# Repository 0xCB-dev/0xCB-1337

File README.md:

# 0xcb-1337
## Mechanical macropad with OLED running QMK

Licence | OSHWA
:-------------------------:|:-------------------------:
 | 

### Available here:

[KeebSupply](https://keeb.supply/products/0xcb-1337)

### QMK:

[keyboards/0xcb/1337/](https://github.com/qmk/qmk_firmware/tree/master/keyboards/0xcb/1337)

#### Flashing:

* `qmk clone`
* `cd qmk_firmware`
* `export LTO=Y`
* Press switch 1 while plugging in to go into dfu mode (or the reset button)
* `make 0xcb/1337:via:flash`

### Assembly:

You can use the [humanpnp](https://files.0xcb.dev/0xCB-1337/humanpnp.html) to easily place components.

### PCB:
KiCad 6 stable release - using these [libs](https://github.com/0xCB-dev/0xcb-libs)

[Schematic](https://github.com/0xCB-dev/0xcb-1337/blob/main/rev4.0/1337-v4.0.pdf)

Top | Bottom
:-------------------------:|:-------------------------:
  |  

### Case 3D files:

[STLs](https://github.com/0xCB-dev/0xcb-1337/tree/main/rev4.0/case/STL)

### PCB 3D files:

[FreeCAD](https://github.com/0xCB-dev/0xcb-1337/tree/main/rev4.0/1337-freecad.FCStd)

[STEP](https://github.com/0xCB-dev/0xcb-1337/tree/main/rev4.0/1337-v4.0.step)

[WRL](https://github.com/0xCB-dev/0xcb-1337/tree/main/rev4.0/1337-v4.0.wrl)

#### BOM:
 References                        | Value        | Quantity | Part Nb.            
-----------------------------------|--------------|----------|---------------------
 C2, C4, C6, C7, C8, C10, C12, C14 | 100n         | 8        | C478888             
 C3, C5, C9                        | 1u           | 3        | C29936              
 C11, C13                          | 22p          | 2        | C85969              
 C1                                | 10u          | 1        | C85713              
 R1, R2                            | 5.1k         | 2        | C23186              
 R3, R4                            | 22           | 2        | C174301             
 R5, R6                            | 10k          | 2        | C98220              
 D1, D2, D3, D4, D5, D6, D7, D8    | SK6812MINI-E | 8        | SK6812MINI-E        
 D10, D11, D12, D13                | WS2812B      | 4        | C114586             
 D9                                | SMF5.0CA     | 1        |  576-SMF5.0CA       
 U2                                | USBLC6-2SC6  | 1        | C7519               
 U3                                | ATMEGA32U4   | 1        | ATMEGA32U4RC-MU-ND  
 Y1                                | 16MHz        | 1        | C389842             
 F1                                | 1A           | 1        | C369150             
 SW1                               | SW_Push      | 1        | C318884             
 FB1, FB2                          | 600R         | 2        | C74330              
 RN1                               | 10k          | 1        | C109324             
 J1                                | USB_IN       | 1        | 900-2169900001CT-ND

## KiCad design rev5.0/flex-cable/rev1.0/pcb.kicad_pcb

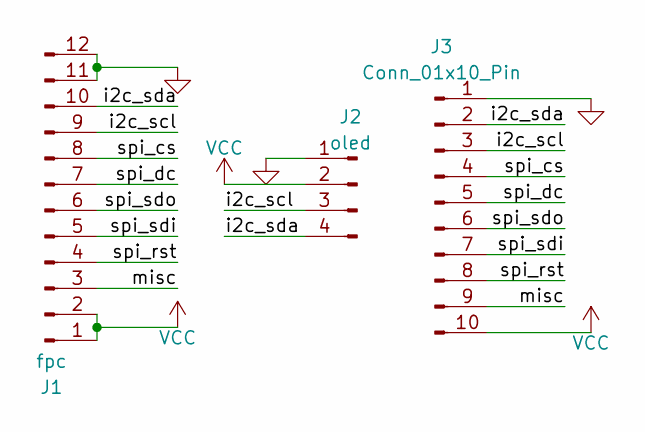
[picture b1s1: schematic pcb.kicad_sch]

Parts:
J1: fpc; FFC-SMD_12P-P0.50_X05B20U12T
J2: oled
J3: Conn_01x10_Pin; PinHeader_1x10_P2.54mm_Vertical

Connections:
/i2c_scl: J1.9, J2.3, J3.3
/i2c_sda: J1.10, J2.4, J3.2
/misc: J1.3, J3.9
/spi_cs: J1.8, J3.4
/spi_dc: J1.7, J3.5
/spi_rst: J1.4, J3.8
/spi_sdi: J1.5, J3.7
/spi_sdo: J1.6, J3.6
GND: J1.11, J1.12, J2.1, J3.1
VCC: J1.1, J1.2, J2.2, J3.10

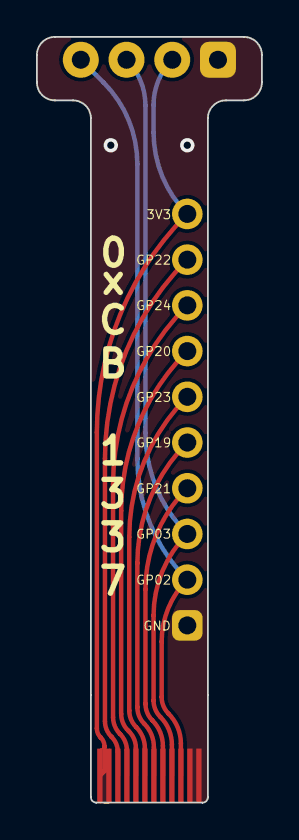
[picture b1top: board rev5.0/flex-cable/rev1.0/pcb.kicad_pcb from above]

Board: 2 copper layers, 12.5 x 42.5 mm, 3 parts (1 on the bottom side), 10 nets.

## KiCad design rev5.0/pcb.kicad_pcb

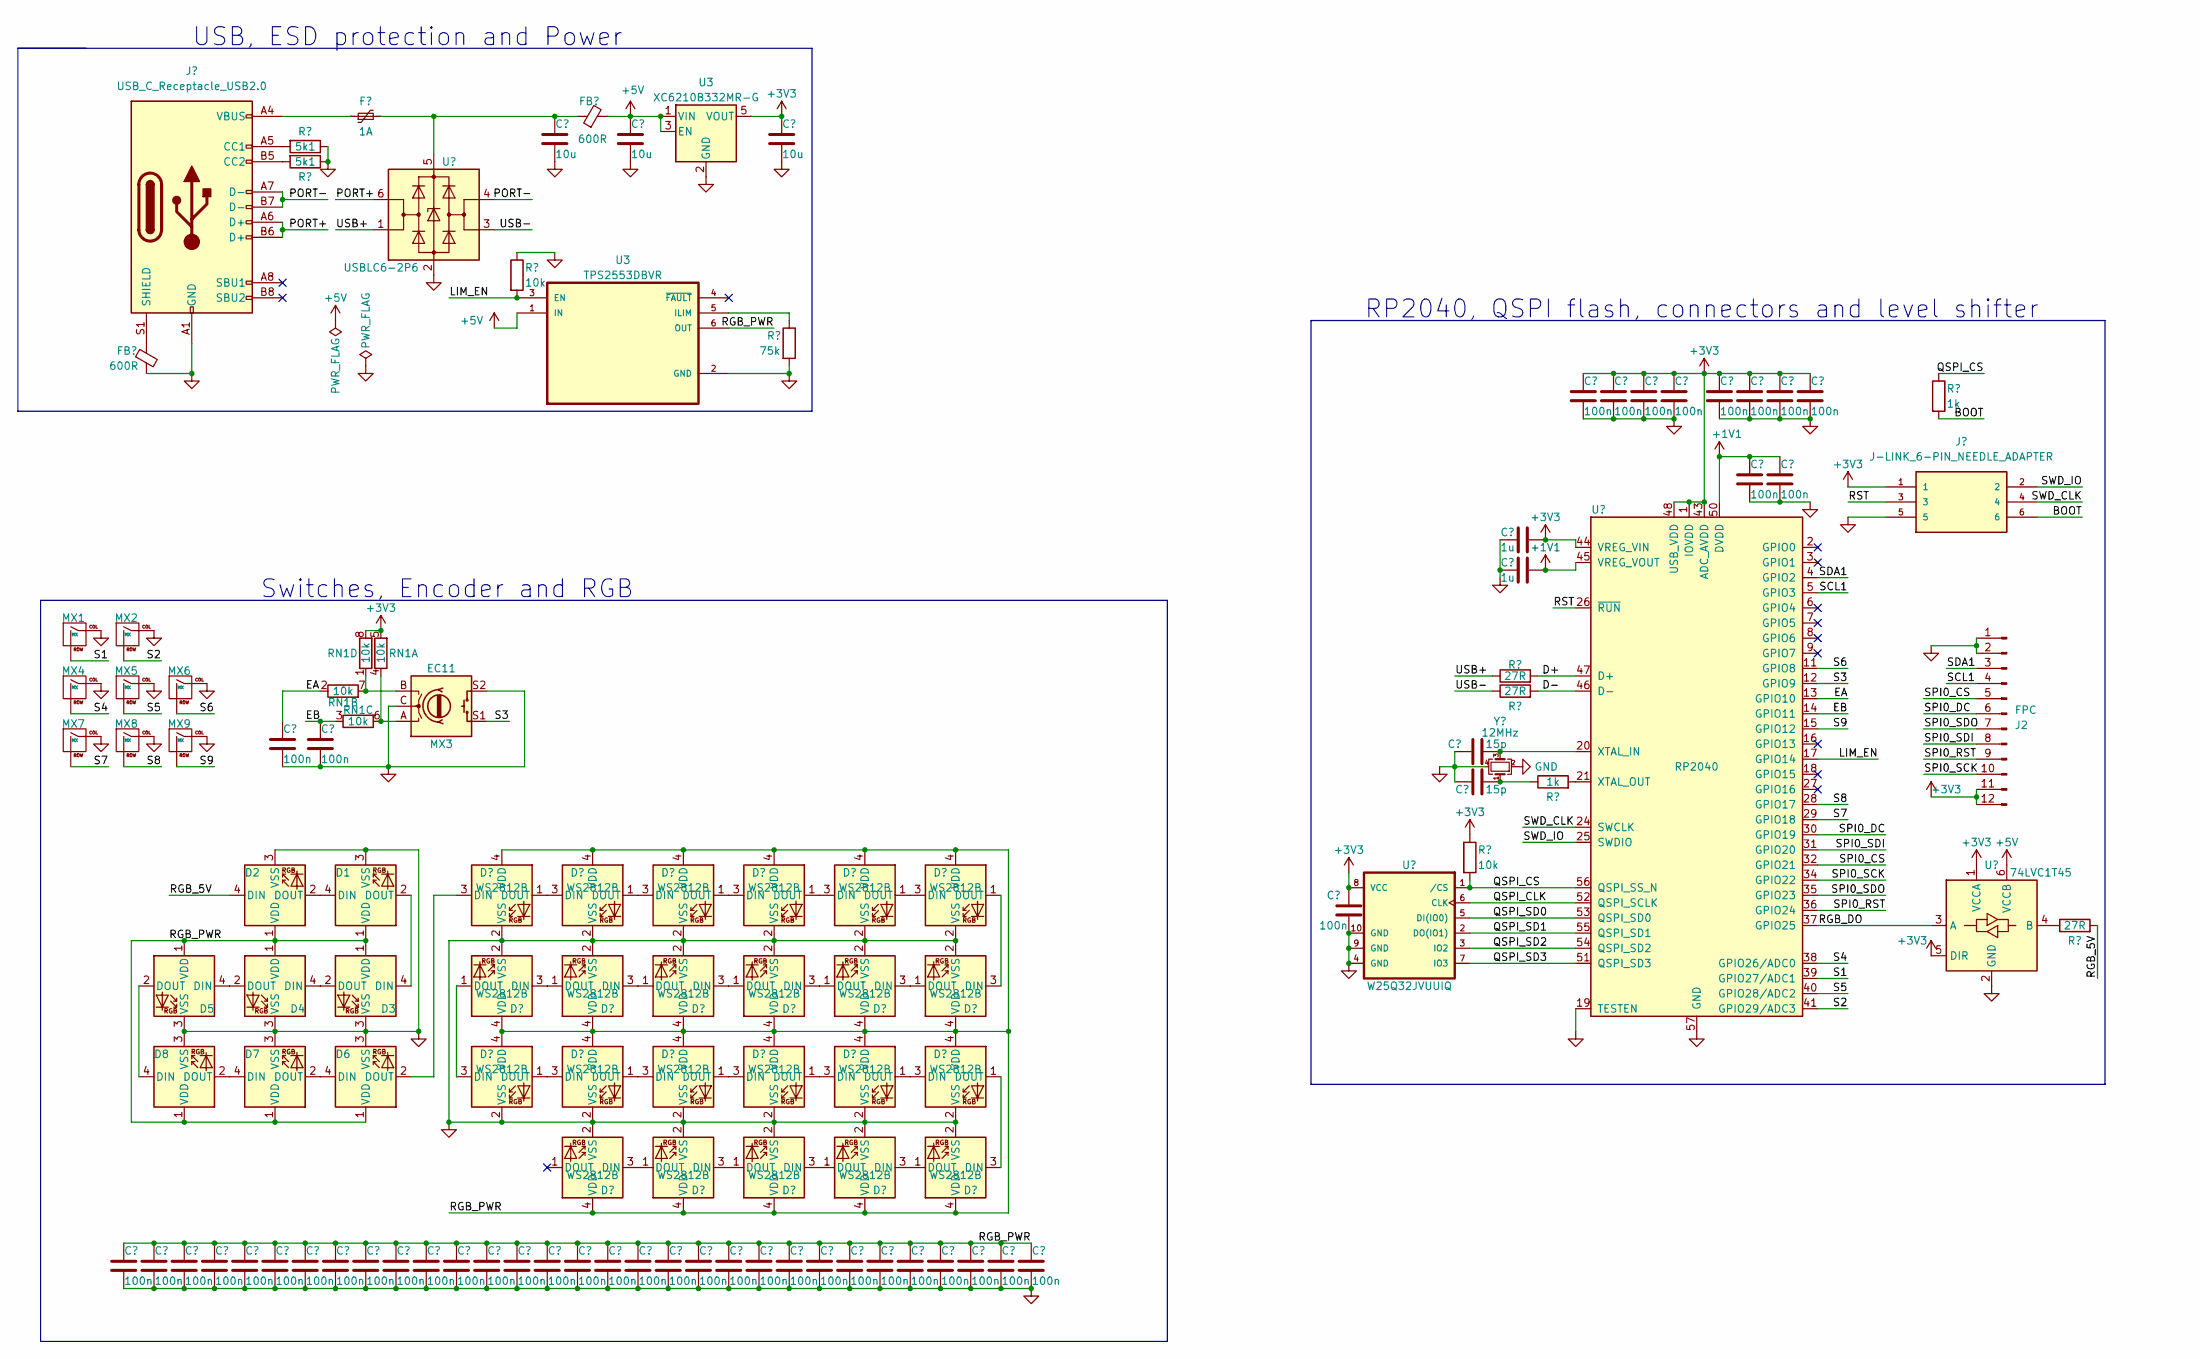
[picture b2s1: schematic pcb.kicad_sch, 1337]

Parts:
C1, C2, C3, C4, C5, C6, C7, C8, C9, C12, C13, C14, C15, C16, C18, C19, C20, C21, C23, C24, C25, C27, C28, C29, C30, C31, C32, C33, C34, C35, C36, C38, C39, C41, C42, C43, C44, C45, C46, C47, C48, C49, C50, C51: 100n; C_0201_0603Metric; MPN CL05B104KO5NNNC; LCSC C576431
C10, C11, C17: 10u; C_0402_1005Metric; MPN CL05A106MQ5NUNC; JLC Basic Y
C22, C26: 1u; C_0201_0603Metric; MPN CL05A105KA5NQNC; LCSC C237458
C37, C40: 15p; C_0201_0603Metric; MPN 0402CG150J500NT; LCSC C85891
D1, D2, D3, D4, D5, D6, D7, D8: SK6812MINI-E; MX_SK6812MINI-E; LCSC C5149201
D9, D10, D11, D12, D13, D14, D15, D16, D17, D18, D19, D20, D21, D22, D23, D24, D25, D26, D27, D28, D29, D30, D31: WS2812B; LED_WS2812B-2020_PLCC4_2.0x2.0mm; MPN WS2812B-2020; LCSC C2976072
F1: 1A; Fuse_0603_1608Metric; MPN MF-FSMF050X-2; LCSC C210357
FB1, FB2: 600R; R_0402_1005Metric; MPN BLM15PX601SN1D; JLC Basic N
J1: USB_C_Receptacle_USB2.0; GT-USB-7014C; MPN GT-USB-7014C; JLC Basic N
J2: FPC; FFC-SMD_12P-P0.50_X05B20U12T; LCSC C388698
J3: J-LINK_6-PIN_NEEDLE_ADAPTER; J-LINK_6-PIN_NEEDLE_ADAPTER_SMALL; MPN TC2030-ALT-NL
MX1, MX2, MX4, MX5, MX6, MX7, MX8, MX9: MX; SW_Hotswap_Kailh_1.00u; LCSC C5156480
MX3: EC11; Part Nb. PEC11L-4125F-S0020-ND; LCSC C143817
R1, R2: 5k1; R_0201_0603Metric; MPN 0402WGF5101TCE; LCSC C473460
R3, R8, R9: 27R; R_0201_0603Metric; MPN 0402WGF270JTCE; LCSC C273295
R4, R7: 10k; R_0201_0603Metric; MPN 0402WGF1002TCE; LCSC C138117
R5: 75k; R_0201_0603Metric; MPN 0402WGF1002TCE; LCSC C25744
R6, R10: 1k; R_0201_0603Metric; MPN 0402WGF1001TCE; LCSC C138165
RN1: 10k; R_Array_Convex_4x0603; Part Nb. MNR14103RTR-ND; LCSC C914793
U1: USBLC6-2P6; SOT-666; MPN USBLC6-2P6; JLC Basic N
U3: TPS2553DBVR; SOT95P280X145-6N; LCSC C55266
U4: 74LVC1T45; SOT-563; MPN SN74LVC1T45DRLR; JLC Basic N
U5: W25Q32JVUUIQ; MPN W25Q32JVUUIQ; LCSC C2999380
U6: RP2040; RP2040-QFN-56; MPN RP2040; LCSC C2040
Y1: 12MHz; Crystal_SMD_2520-4Pin_2.5x2.0mm; MPN 2TJ412000HYGBC; LCSC C2149204

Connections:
+1V1: C22.2, C25.1, C39.1, U6.23 (DVDD), U6.45 (VREG_VOUT), U6.50 (DVDD)
/BOOT: J3.6, R6.2
/D+: R8.2, U6.47 (D+)
/D-: R9.2, U6.46 (D-)
/EA: C7.1, RN1.2 (R2.1), U6.13 (GPIO10)
/EB: C8.1, RN1.3 (R3.1), U6.14 (GPIO11)
/PORT+: J1.A6 (D+), J1.B6 (D+), U1.6 (I/O1)
/PORT-: J1.A7 (D-), J1.B7 (D-), U1.4 (I/O2)
/QSPI_CLK: U5.6 (CLK), U6.52 (QSPI_SCLK)
/QSPI_CS: R6.1, R7.2, U5.1 (/CS), U6.56 (QSPI_SS_N)
/QSPI_SD0: U5.5 (DI(IO0)), U6.53 (QSPI_SD0)
/QSPI_SD1: U5.2 (DO(IO1)), U6.55 (QSPI_SD1)
/QSPI_SD2: U5.3 (IO2), U6.54 (QSPI_SD2)
/QSPI_SD3: U5.7 (IO3), U6.51 (QSPI_SD3)
/RGB_5V: D2.4 (DIN), R3.2
/RGB_DO: U4.3 (A), U6.37 (GPIO25)
/RGB_PWR: C1.1, C2.1, C3.1, C4.1, C5.1, C6.1, C9.1, C12.1, C13.1, C14.1, C15.1, C16.1, C18.1, C19.1, C20.1, C28.1, C29.1, C30.1, C31.1, C36.1, C41.1, C42.1, C43.1, C44.1, C45.1, C46.1, C47.1, C48.1, C49.1, C50.1, C51.1, D1.1 (VDD), D2.1 (VDD), D3.1 (VDD), D4.1 (VDD), D5.1 (VDD), D6.1 (VDD), D7.1 (VDD), D8.1 (VDD), D9.4 (VDD), D10.4 (VDD), D11.4 (VDD), D12.4 (VDD), D13.4 (VDD), D14.4 (VDD), D15.4 (VDD), D16.4 (VDD), D17.4 (VDD), D18.4 (VDD), D19.4 (VDD), D20.4 (VDD), D21.4 (VDD), D22.4 (VDD), D23.4 (VDD), D24.4 (VDD), D25.4 (VDD), D26.4 (VDD), D27.4 (VDD), D28.4 (VDD), D29.4 (VDD), D30.4 (VDD), D31.4 (VDD), U3.6 (OUT)
/RST: J3.3, U6.26 (~RUN)
/S1: MX1.2 (ROW), U6.39 (GPIO27/ADC1)
/S2: MX2.2 (ROW), U6.41 (GPIO29/ADC3)
/S3: MX3.S1, U6.12 (GPIO9)
/S4: MX4.2 (ROW), U6.38 (GPIO26/ADC0)
/S5: MX5.2 (ROW), U6.40 (GPIO28/ADC2)
/S6: MX6.2 (ROW), U6.11 (GPIO8)
/S7: MX7.2 (ROW), U6.29 (GPIO18)
/S8: MX8.2 (ROW), U6.28 (GPIO17)
/S9: MX9.2 (ROW), U6.15 (GPIO12)
/SCL1: J2.4, U6.5 (GPIO3)
/SDA1: J2.3, U6.4 (GPIO2)
/SPI0_CS: J2.5, U6.32 (GPIO21)
/SPI0_DC: J2.6, U6.30 (GPIO19)
/SPI0_RST: J2.9, U6.36 (GPIO24)
/SPI0_SCK: J2.10, U6.34 (GPIO22)
/SPI0_SDI: J2.8, U6.31 (GPIO20)
/SPI0_SDO: J2.7, U6.35 (GPIO23)
/SWD_CLK: J3.4, U6.24 (SWCLK)
/SWD_IO: J3.2, U6.25 (SWDIO)
/USB+: R8.1, U1.1 (I/O1)
/USB-: R9.1, U1.3 (I/O2)
GND: C1.2, C2.2, C3.2, C4.2, C5.2, C6.2, C7.2, C8.2, C9.2, C10.2, C11.2, C12.2, C13.2, C14.2, C15.2, C16.2, C17.2, C18.2, C19.2, C20.2, C21.2, C22.1, C23.2, C24.2, C25.2, C26.1, C27.2, C28.2, C29.2, C30.2, C31.2, C32.2, C33.2, C34.2, C35.2, C36.2, C37.1, C38.2, C39.2, C40.1, C41.2, C42.2, C43.2, C44.2, C45.2, C46.2, C47.2, C48.2, C49.2, C50.2, C51.2, D1.3 (VSS), D2.3 (VSS), D3.3 (VSS), D4.3 (VSS), D5.3 (VSS), D6.3 (VSS), D7.3 (VSS), D8.3 (VSS), D9.2 (VSS), D10.2 (VSS), D11.2 (VSS), D12.2 (VSS), D13.2 (VSS), D14.2 (VSS), D15.2 (VSS), D16.2 (VSS), D17.2 (VSS), D18.2 (VSS), D19.2 (VSS), D20.2 (VSS), D21.2 (VSS), D22.2 (VSS), D23.2 (VSS), D24.2 (VSS), D25.2 (VSS), D26.2 (VSS), D27.2 (VSS), D28.2 (VSS), D29.2 (VSS), D30.2 (VSS), D31.2 (VSS), FB1.2, J1.A1 (GND), J1.A12 (GND), J1.B1 (GND), J1.B12 (GND), J2.1, J2.2, J3.5, MX1.1 (COL), MX2.1 (COL), MX3.C, MX3.S2, MX4.1 (COL), MX5.1 (COL), MX6.1 (COL), MX7.1 (COL), MX8.1 (COL), MX9.1 (COL), R1.1, R2.1, R4.1, R5.2, U1.2 (GND), U3.2 (GND), U4.2 (GND), U5.4 (GND), U5.9 (GND), U5.10 (GND), U6.19 (TESTEN), U6.57 (GND), Y1.2, Y1.4; also elsewhere on the board
unnamed: C40.2, R10.1, Y1.1
unnamed: D1.4 (DIN), D2.2 (DOUT)
unnamed: D1.2 (DOUT), D3.4 (DIN)
unnamed: D3.2 (DOUT), D4.4 (DIN)
unnamed: D4.2 (DOUT), D5.4 (DIN)
unnamed: D5.2 (DOUT), D8.4 (DIN)
unnamed: D6.4 (DIN), D7.2 (DOUT)
unnamed: D7.4 (DIN), D8.2 (DOUT)
unnamed: D9.1 (DOUT), D10.3 (DIN)
unnamed: D10.1 (DOUT), D11.3 (DIN)
unnamed: D11.1 (DOUT), D12.3 (DIN)
unnamed: D12.1 (DOUT), D13.3 (DIN)
unnamed: D13.1 (DOUT), D15.3 (DIN)
unnamed: D14.3 (DIN), D16.1 (DOUT)
unnamed: D9.3 (DIN), D14.1 (DOUT)
unnamed: D15.1 (DOUT), D17.3 (DIN)
unnamed: D16.3 (DIN), D18.1 (DOUT)
unnamed: D17.1 (DOUT), D19.3 (DIN)
unnamed: D18.3 (DIN), D20.1 (DOUT)
unnamed: D19.1 (DOUT), D21.3 (DIN)
unnamed: D20.3 (DIN), D22.1 (DOUT)
unnamed: D21.1 (DOUT), D23.3 (DIN)
unnamed: D22.3 (DIN), D24.1 (DOUT)
unnamed: D23.1 (DOUT), D25.3 (DIN)
unnamed: D24.3 (DIN), D26.1 (DOUT)
unnamed: D26.3 (DIN), D27.1 (DOUT)
unnamed: D27.3 (DIN), D28.1 (DOUT)
unnamed: D28.3 (DIN), D29.1 (DOUT)
unnamed: D29.3 (DIN), D30.1 (DOUT)
unnamed: D30.3 (DIN), D31.1 (DOUT)
unnamed: D6.2 (DOUT), D31.3 (DIN)
unnamed: F1.1, J1.A4 (VBUS), J1.A9 (VBUS), J1.B4 (VBUS), J1.B9 (VBUS)
unnamed: J1.A5 (CC1), R2.2
unnamed: J1.B5 (CC2), R1.2
unnamed: FB1.1, J1.S1 (SHIELD)
unnamed: MX3.B, RN1.1 (R1.1), RN1.7 (R2.2)
unnamed: MX3.A, RN1.4 (R4.1), RN1.6 (R3.2)
unnamed: C10.1, F1.2, FB2.1, U1.5 (VBUS)
unnamed: R3.1, U4.4 (B)
unnamed: C37.2, U6.20 (XTAL_IN), Y1.3
unnamed: R10.2, U6.21 (XTAL_OUT)

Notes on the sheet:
Switches, Encoder and RGB
USB, ESD protection and Power
RP2040, QSPI flash, connectors and level shifter

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
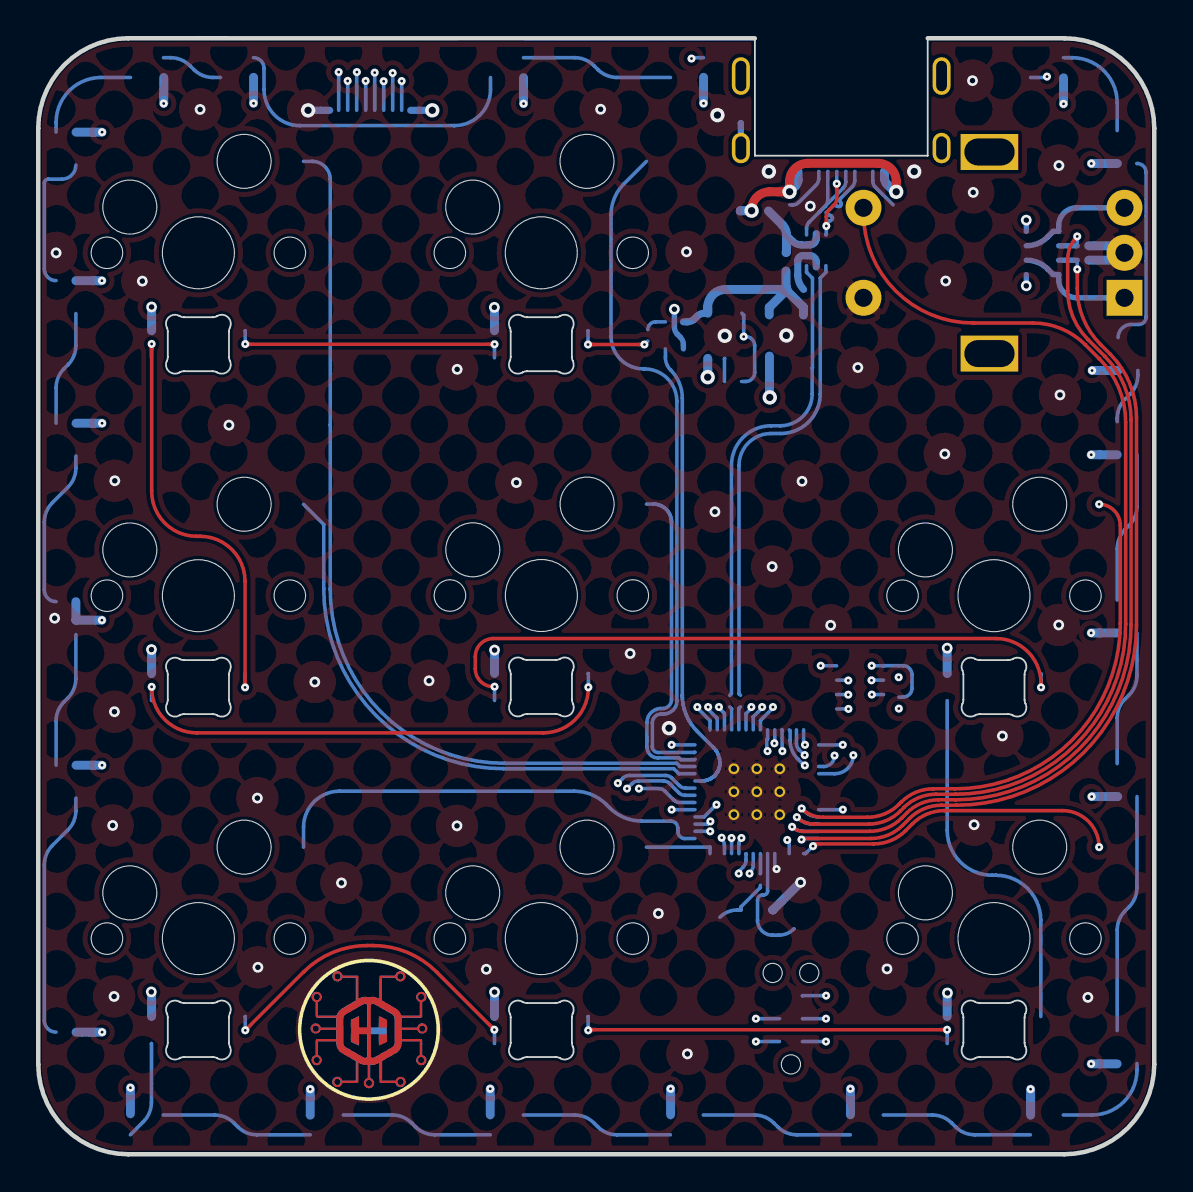
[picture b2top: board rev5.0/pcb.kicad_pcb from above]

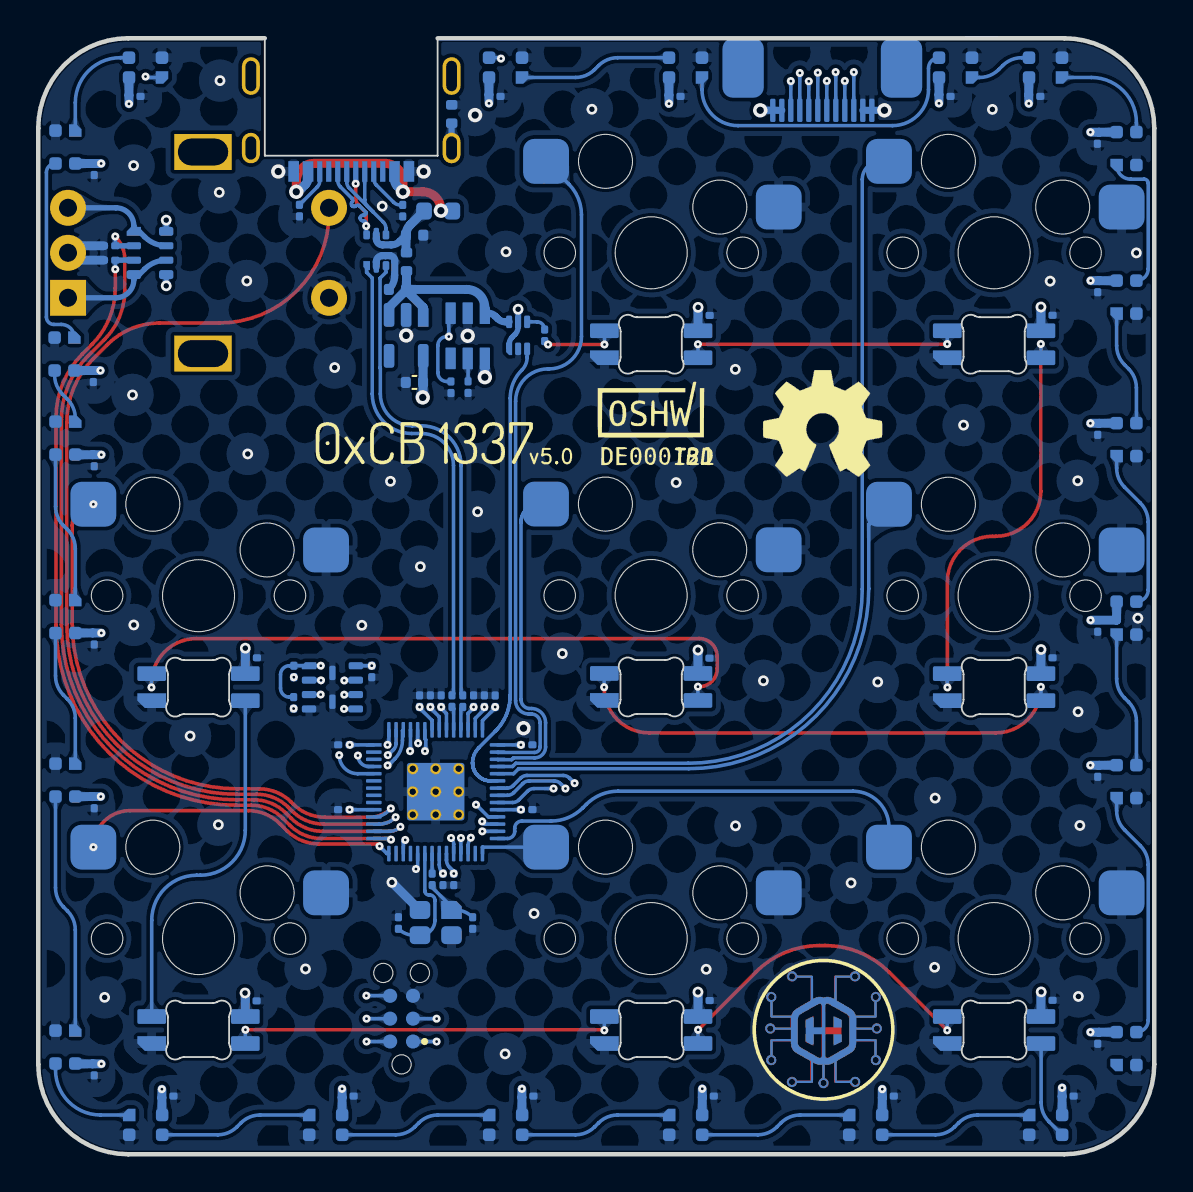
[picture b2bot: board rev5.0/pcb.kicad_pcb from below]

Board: 4 copper layers, 62.0 x 62.0 mm, 116 parts (115 on the bottom side), 85 nets.

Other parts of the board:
U2: XC6210B332MR-G; SOT-23-5
kibuzzard-1: G***; kibuzzard-61BA68AC

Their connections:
GND: U2.2 (GND); also elsewhere on the board

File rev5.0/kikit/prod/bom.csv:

Comment,Designator,Footprint,LCSC
100n,"C1,C2,C3,C4,C5,C6,C7,C8,C9,C12,C13,C14,C15,C16,C18,C19,C20,C21,C23,C24,C25,C27,C28,C29,C30,C31,C32,C33,C34,C35,C36,C38,C39,C41,C42,C43,C44,C45,C46,C47,C48,C49,C50,C51",Capacitor_SMD:C_0201_0603Metric,C576431
1u,"C22,C26",Capacitor_SMD:C_0201_0603Metric,C237458
TPS2553DBVR,U3,0xcb:SOT95P280X145-6N,C55266
SK6812MINI-E,"D1,D2,D3,D4,D5,D6,D7,D8",0xcb:MX_SK6812MINI-E,C5149201
WS2812B,"D9,D10,D11,D12,D13,D14,D15,D16,D17,D18,D19,D20,D21,D22,D23,D24,D25,D26,D27,D28,D29,D30,D31",LED_SMD:LED_WS2812B-2020_PLCC4_2.0x2.0mm,C2976072
MX,"MX1,MX2,MX4,MX5,MX6,MX7,MX8,MX9",0xcb:SW_Hotswap_Kailh_1.00u,C5156480
10k,"R4,R7",Resistor_SMD:R_0201_0603Metric,C138117
USB_C_Receptacle_USB2.0,J1,0xcb:GT-USB-7014C,C963373
12MHz,Y1,Crystal:Crystal_SMD_2520-4Pin_2.5x2.0mm,C2149204
5k1,"R1,R2",Resistor_SMD:R_0201_0603Metric,C473460
FPC,J2,0xcb:FFC-SMD_12P-P0.50_X05B20U12T,C388698
10u,"C10,C11,C17",Capacitor_SMD:C_0402_1005Metric,C15525
EC11,MX3,0xcb:EC11,C143817
27R,"R3,R8,R9",Resistor_SMD:R_0201_0603Metric,C273295
600R,"FB1,FB2",Resistor_SMD:R_0402_1005Metric,C160977
75k,R5,Resistor_SMD:R_0201_0603Metric,C25744
10k,RN1,Resistor_SMD:R_Array_Convex_4x0603,C914793
XC6210B332MR-G,U2,Package_TO_SOT_SMD:SOT-23-5,C47719
15p,"C37,C40",Capacitor_SMD:C_0201_0603Metric,C85891
RP2040,U6,0xcb:RP2040-QFN-56,C2040
1k,"R6,R10",Resistor_SMD:R_0201_0603Metric,C138165
W25Q32JVUUIQ,U5,0xcb:W25Q32JVUUIQ,C2999380
1A,F1,Fuse:Fuse_0603_1608Metric,C210357
USBLC6-2P6,U1,Package_TO_SOT_SMD:SOT-666,C2827693
74LVC1T45,U4,Package_TO_SOT_SMD:SOT-563,C352970

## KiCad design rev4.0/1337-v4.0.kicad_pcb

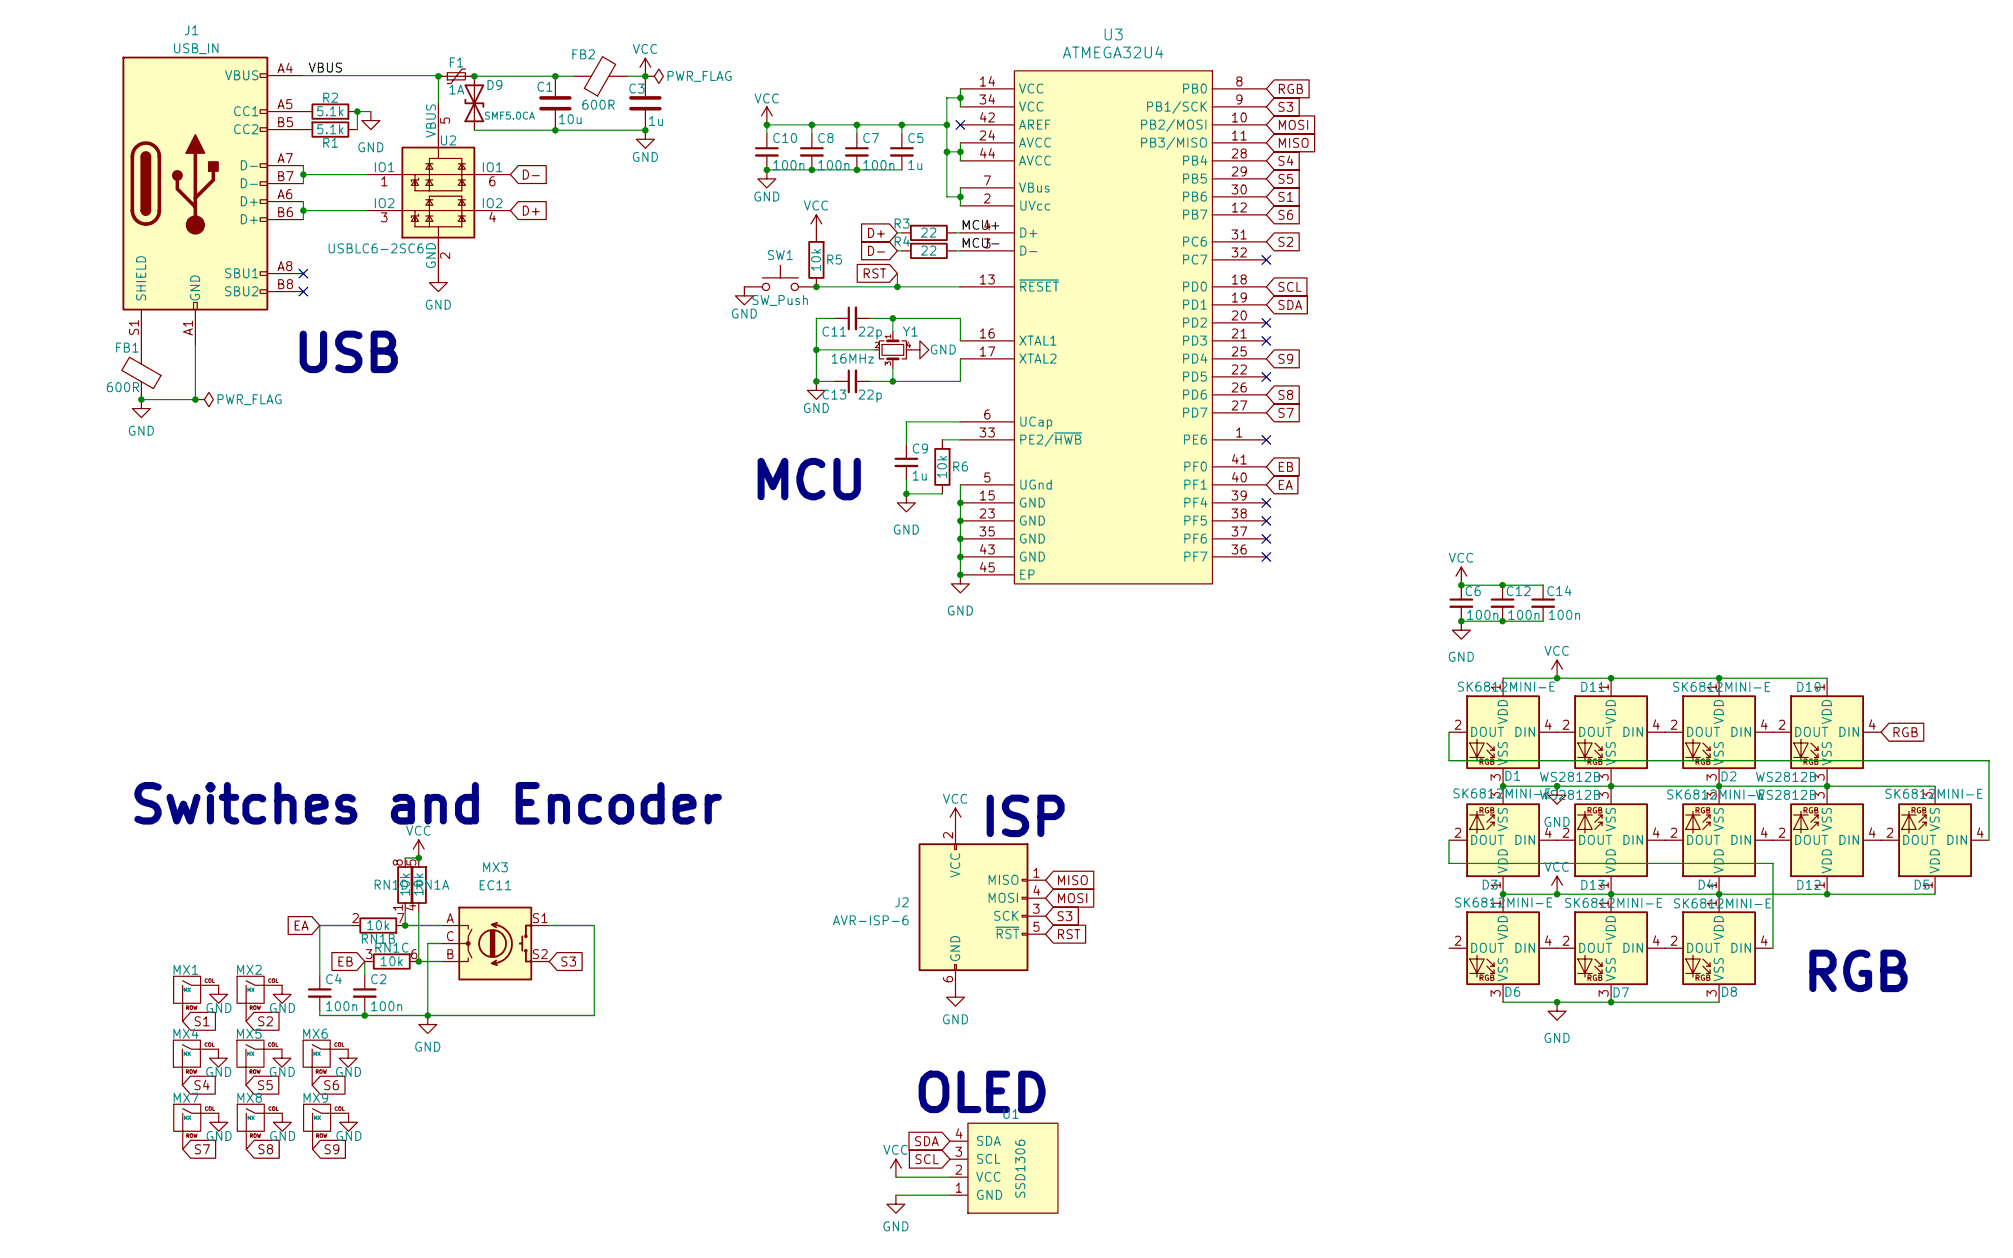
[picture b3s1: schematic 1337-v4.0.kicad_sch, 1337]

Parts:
C1: 10u; C_0603_1608Metric
C2, C4, C6, C7, C8, C10, C12, C14: 100n; C_0603_1608Metric; Part Nb. 478-5266-1-ND
C3: 1u; C_0603_1608Metric
C5, C9: 1u; C_0603_1608Metric; Part Nb. 1276-1102-1-ND
C11, C13: 22p; C_0603_1608Metric; Part Nb. 478-1167-1-ND
D1, D2, D3, D4, D5, D6, D7, D8: SK6812MINI-E; MX_SK6812MINI-E
D9: SMF5.0CA; D_SOD-123F
D10, D11, D12, D13: WS2812B; LED_WS2812B_PLCC4_5.0x5.0mm_P3.2mm; Part Nb. 1568-COM-16347CT-ND
F1: 1A; Fuse_0805_2012Metric; Part Nb. 507-1815-1-ND
FB1: 600R; Ferrite_Bead_0603; Part Nb. 732-1593-1-ND
FB2: 600R; Ferrite_Bead_0603
J1: USB_IN; molex2169900001; Part Nb. 900-2169900002CT-ND
J2: AVR-ISP-6; AVR_PROG_2.54_THT
MX1, MX2, MX4, MX5, MX6, MX7, MX8, MX9: MX; SW_Cherry_MX_PCB_1.00u
MX3: EC11; Part Nb. PEC11L-4125F-S0020-ND
R1, R2: 5.1k; R_0603_1608Metric; Part Nb. P5.1KDBCT-ND
R3, R4: 22; R_0603_1608Metric; Part Nb. A130081CT-ND
R5, R6: 10k; R_0603_1608Metric; Part Nb. RHM10KADCT-ND
RN1: 10k; R_Array_Convex_4x0603; Part Nb. MNR14103RTR-ND
SW1: SW_Push; SW_SPST_TL3342; Part Nb. EG2531CT-ND
U1: SSD1306; 128x64OLED
U2: USBLC6-2SC6; SOT-23-6; Part Nb. 497-5235-1-ND
U3: ATMEGA32U4; QFN-44-1EP_7x7mm_P0.5mm_EP5.2x5.2mm_ThermalVias; Part Nb. ATMEGA32U4RC-MURCT-ND
Y1: 16MHz; Crystal_SMD_3225-4Pin_3.2x2.5mm; Part Nb. XC2060CT-ND

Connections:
/MCU+: R3.1, U3.4 (D+)
/MCU-: R4.1, U3.3 (D-)
/VBUS: F1.1, J1.A4 (VBUS), J1.A9 (VBUS), J1.B4 (VBUS), J1.B9 (VBUS), U2.5 (VBUS)
D+: R3.2, U2.4 (IO2)
D-: R4.2, U2.6 (IO1)
EA: C4.1, RN1.2 (R2.1), U3.40 (PF1)
EB: C2.1, RN1.3 (R3.1), U3.41 (PF0)
GND: C1.2, C2.2, C3.2, C4.2, C5.2, C6.2, C7.2, C8.2, C9.2, C10.2, C11.1, C12.2, C13.1, C14.2, D1.3 (VSS), D2.3 (VSS), D3.3 (VSS), D4.3 (VSS), D5.3 (VSS), D6.3 (VSS), D7.3 (VSS), D8.3 (VSS), D9.1 (A1), D10.3 (VSS), D11.3 (VSS), D12.3 (VSS), D13.3 (VSS), FB1.1, J1.A1 (GND), J1.A12 (GND), J1.B1 (GND), J1.B12 (GND), J2.6 (GND), MX1.1 (COL), MX2.1 (COL), MX3.C, MX3.S1, MX4.1 (COL), MX5.1 (COL), MX6.1 (COL), MX7.1 (COL), MX8.1 (COL), MX9.1 (COL), R1.1, R2.2, R6.1, SW1.1, U1.1 (GND), U2.2 (GND), U3.5 (UGnd), U3.15 (GND), U3.23 (GND), U3.35 (GND), U3.43 (GND), U3.45 (EP), Y1.2, Y1.4
MISO: J2.1 (MISO), U3.11 (PB3/MISO)
MOSI: J2.4 (MOSI), U3.10 (PB2/MOSI)
unnamed: C1.1, D9.2 (A2), F1.2, FB2.1
unnamed: C9.1, U3.6 (UCap)
unnamed: C11.2, U3.16 (XTAL1), Y1.1
unnamed: C13.2, U3.17 (XTAL2), Y1.3
unnamed: D1.2 (DOUT), D5.4 (DIN)
unnamed: D1.4 (DIN), D11.2 (DOUT)
unnamed: D3.2 (DOUT), D8.4 (DIN)
unnamed: D6.4 (DIN), D7.2 (DOUT)
unnamed: D7.4 (DIN), D8.2 (DOUT)
unnamed: D2.4 (DIN), D10.2 (DOUT)
unnamed: D2.2 (DOUT), D11.4 (DIN)
unnamed: D4.4 (DIN), D12.2 (DOUT)
unnamed: D5.2 (DOUT), D12.4 (DIN)
unnamed: D3.4 (DIN), D13.2 (DOUT)
unnamed: D4.2 (DOUT), D13.4 (DIN)
unnamed: FB1.2, J1.S1 (SHIELD)
unnamed: J1.A5 (CC1), R2.1
unnamed: J1.A6 (D+), J1.B6 (D+), U2.3 (IO2)
unnamed: J1.A7 (D-), J1.B7 (D-), U2.1 (IO1)
unnamed: J1.B5 (CC2), R1.2
unnamed: MX3.A, RN1.1 (R1.1), RN1.7 (R2.2)
unnamed: MX3.B, RN1.4 (R4.1), RN1.6 (R3.2)
unnamed: R6.2, U3.33 (PE2/~HWB)
RGB: D10.4 (DIN), U3.8 (PB0)
RST: J2.5 (~RST), R5.1, SW1.2, U3.13 (~RESET)
S1: MX1.2 (ROW), U3.30 (PB6)
S2: MX2.2 (ROW), U3.31 (PC6)
S3: J2.3 (SCK), MX3.S2, U3.9 (PB1/SCK)
S4: MX4.2 (ROW), U3.28 (PB4)
S5: MX5.2 (ROW), U3.29 (PB5)
S6: MX6.2 (ROW), U3.12 (PB7)
S7: MX7.2 (ROW), U3.27 (PD7)
S8: MX8.2 (ROW), U3.26 (PD6)
S9: MX9.2 (ROW), U3.25 (PD4)
SCL: U1.3 (SCL), U3.18 (PD0)
SDA: U1.4 (SDA), U3.19 (PD1)
VCC: C3.1, C5.1, C6.1, C7.1, C8.1, C10.1, C12.1, C14.1, D1.1 (VDD), D2.1 (VDD), D3.1 (VDD), D4.1 (VDD), D5.1 (VDD), D6.1 (VDD), D7.1 (VDD), D8.1 (VDD), D10.1 (VDD), D11.1 (VDD), D12.1 (VDD), D13.1 (VDD), FB2.2, J2.2 (VCC), R5.2, RN1.5 (R4.2), RN1.8 (R1.2), U1.2 (VCC), U3.2 (UVcc), U3.7 (VBus), U3.14 (VCC), U3.24 (AVCC), U3.34 (VCC), U3.44 (AVCC)

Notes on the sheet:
RGB
ISP
OLED
USB
MCU
Switches and Encoder

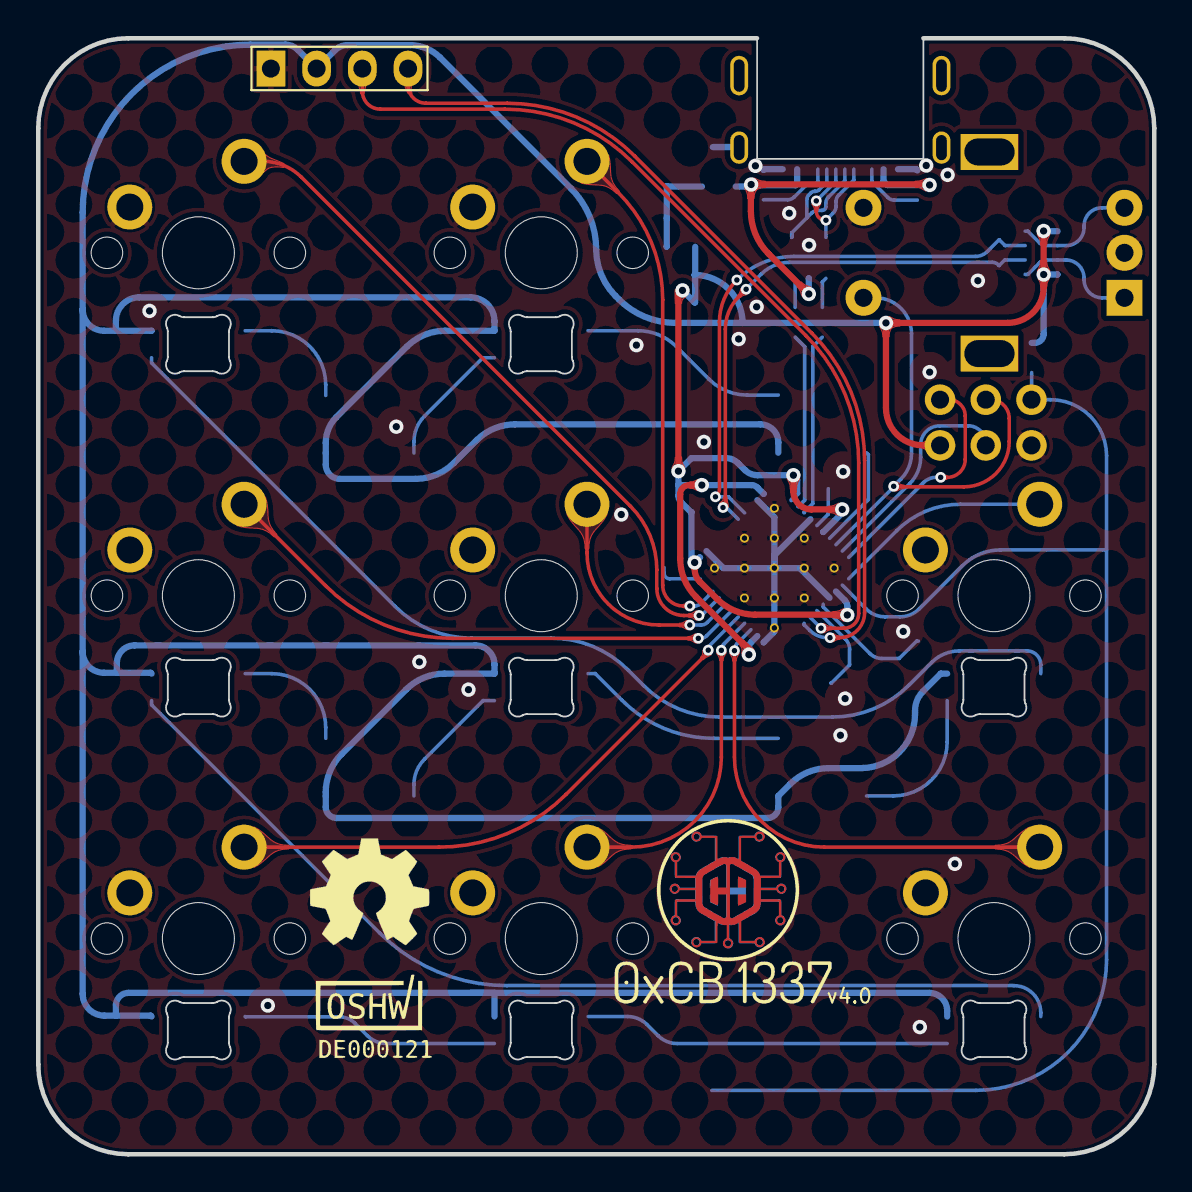
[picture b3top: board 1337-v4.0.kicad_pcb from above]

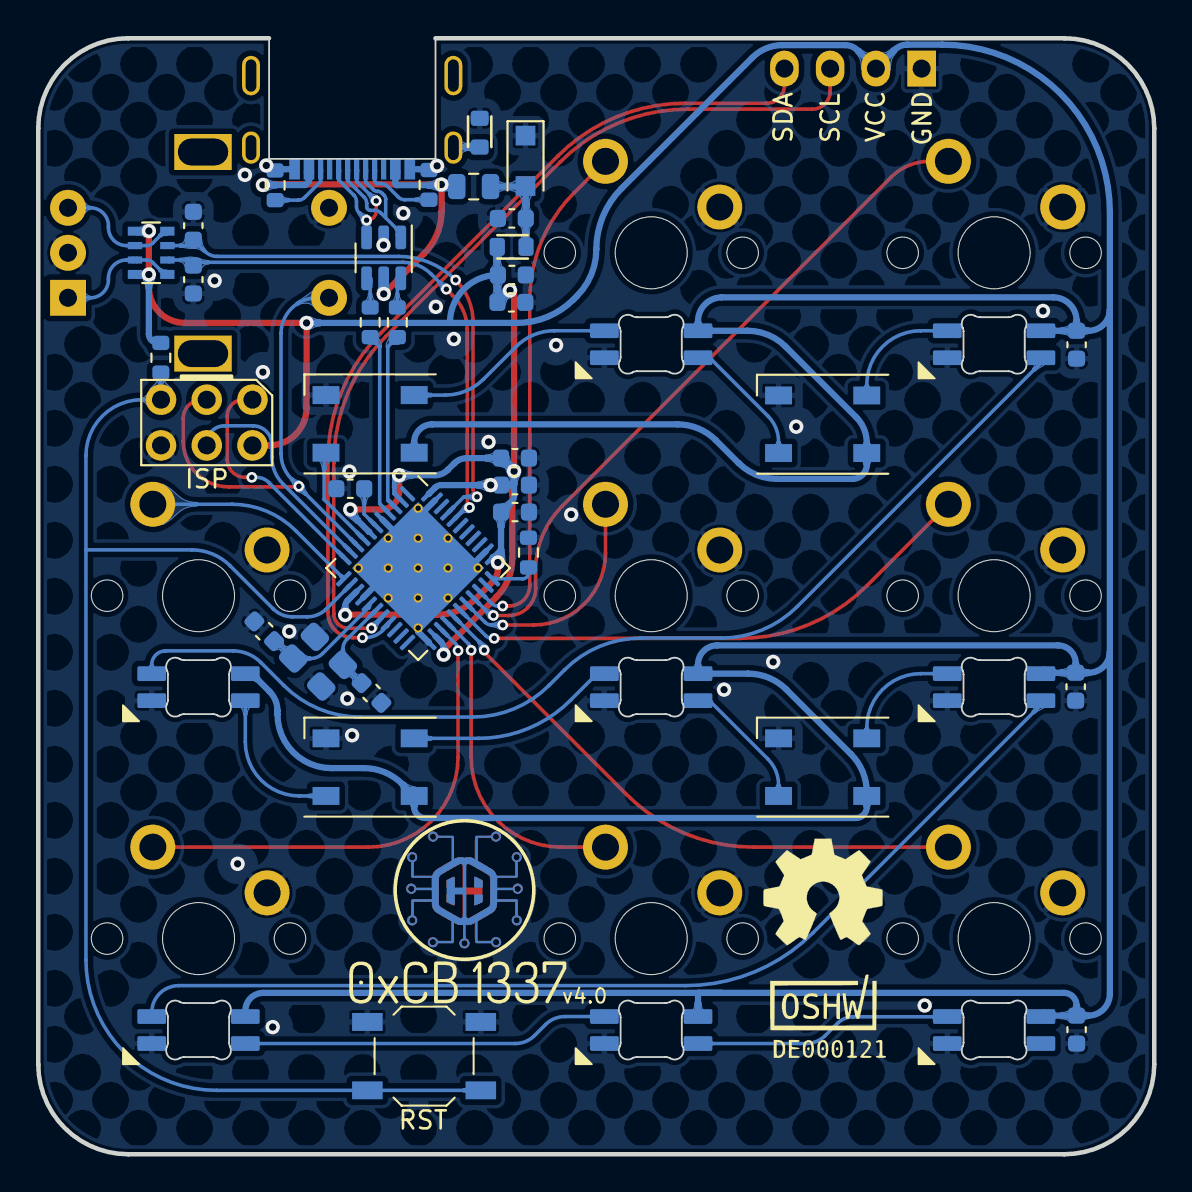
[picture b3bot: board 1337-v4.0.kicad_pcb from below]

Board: 2 copper layers, 62.0 x 62.0 mm, 55 parts (36 on the bottom side), 47 nets.

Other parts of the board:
kibuzzard-61BA68AC, kibuzzard-61BA68AC#2: G***; kibuzzard-61BA68AC
